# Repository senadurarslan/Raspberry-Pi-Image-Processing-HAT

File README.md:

# Raspberry Pi Image Processing HAT

A custom **Raspberry Pi 4 Model B HAT** designed for image capture, processing, and display using an **ArduCAM OV2640 camera**, **ST7735 TFT display**, and an **LM2596S-3.3 based switching power supply**.

## Project Overview

This project focuses on the design and implementation of a custom Hardware Attached on Top (**HAT**) board for the Raspberry Pi 4 Model B.

The system captures images using an **ArduCAM OV2640 camera**, processes the image data on the Raspberry Pi, and displays the resulting output on an **ST7735 TFT display**.

A custom PCB was designed to integrate the camera, display, Raspberry Pi GPIO interface, and power management circuitry into a compact embedded vision platform.

The main hardware blocks are:

- **Processing Unit:** Raspberry Pi 4 Model B
- **Image Capture:** ArduCAM Mini OV2640
- **Display:** ST7735 TFT
- **Power Management:** LM2596S-3.3 based SMPS
- **Custom Hardware:** Raspberry Pi HAT PCB

---

## System Architecture

The Raspberry Pi acts as the main processing and control unit.

The **ArduCAM OV2640** communicates with the Raspberry Pi using:

- **I²C** for camera sensor configuration
- **SPI** for image data transfer

The **ST7735 TFT display** uses:

- **SPI** for command and pixel data transfer
- GPIO signals for display control and reset

The overall image processing flow is:

```text
        ArduCAM OV2640
              │
       ┌──────┴──────┐
       │             │
      I²C           SPI
Configuration    Image Data
       │             │
       └──────┬──────┘
              ▼
       Raspberry Pi 4
              │
       JPEG Acquisition
              │
       Buffer Processing
              │
        JPEG Decoding
              │
       RGB565 Conversion
              │
              ▼
       ST7735 TFT Display
```

---

## Hardware Design

The custom HAT PCB was designed using **KiCad EDA**.

The hardware design includes:

- Raspberry Pi 40-pin GPIO interface
- ArduCAM OV2640 camera connector
- ST7735 TFT display connector
- LM2596S-3.3 switching regulator
- SPI communication lines
- I²C communication lines
- Dedicated chip-select signals
- Power distribution circuitry
- Ground plane for improved signal integrity
- SMD and THT components

The PCB was designed as a **two-layer board** and manufactured using the generated Gerber files.

After production, the components were assembled and the board was mounted directly onto the Raspberry Pi for functional testing.

---

## Power Management

An **LM2596S-3.3 based switching power supply (SMPS)** was integrated into the HAT design.

The power stage converts the available supply voltage to the required **3.3 V rail** for the peripheral hardware.

A switching regulator was preferred to provide:

- Higher energy efficiency
- Reduced thermal losses
- Stable output voltage
- Better performance under varying current loads
- Improved suitability for embedded applications

---

## Software Architecture

The software was developed using **C and C++** on Raspberry Pi OS.

The implementation includes:

- ArduChip communication
- OV2640 sensor initialization
- I²C communication
- SPI communication
- JPEG image acquisition
- JPEG file storage
- JPEG decoding
- RGB565 image conversion
- ST7735 TFT display control
- Camera and display integration
- Hardware test programs

### Main Source Files

```text
arduchip.c
arduchip.h

ov2640.c
ov2640.h
ov2640_regs.c
ov2640_regs.h

spi_linux.c
spi_linux.h

i2c_linux.c
i2c_linux.h

jpeg_to_rgb565.c
jpeg_to_rgb565.h

capture_to_file.c
capture_to_screen.cpp
decode_test.c

test_arduchip.c
test_hal.c
```

---

## Build System

The project includes a **Makefile** for compiling and running the camera, image processing, and TFT applications.

### Compilers

The project uses:

```text
gcc
g++
```

The full camera-to-display application is compiled using:

```text
-std=gnu++20
```

### Libraries

The TFT application uses:

```text
rpidisplaygl
lgpio
librt
```

with:

```text
/usr/local/include
/usr/local/lib
```

---

## Build & Run

### Show Available Commands

```bash
make
```

The default target displays the available build and run commands.

### Clean Build Files

```bash
make clean
```

This removes generated object files, executables, and temporary image files such as:

```text
frame.jpg
frame.rgb565
```

---

### ArduChip SPI Test

Compile:

```bash
make test_arduchip
```

Run:

```bash
make run_test_arduchip
```

This test verifies communication with the ArduChip interface.

---

### OV2640 Initialization Test

Compile:

```bash
make test_hal
```

Run:

```bash
make run_test_hal
```

This test verifies OV2640 initialization and communication through the hardware abstraction layer.

---

### Capture JPEG Image

Compile:

```bash
make capture_app
```

Run:

```bash
make run_capture_app
```

The application captures an image from the OV2640 camera and stores the acquired JPEG data.

---

### JPEG to RGB565 Conversion

Compile:

```bash
make decode_test
```

Run:

```bash
make run_decode_test
```

This application tests the conversion of captured JPEG image data into the **RGB565** pixel format used by the TFT display.

---

### Full Camera-to-TFT Pipeline

Compile:

```bash
make capture_screen
```

Run:

```bash
make run_capture_screen
```

This application combines the complete image pipeline:

```text
Camera
  ↓
JPEG Capture
  ↓
Image Processing
  ↓
RGB565 Conversion
  ↓
ST7735 TFT
```

---

# Project Gallery

## Final Integrated HAT System

The final implementation combines the custom HAT PCB, **ArduCAM OV2640 camera**, **ST7735 TFT display**, onboard power stage, and Raspberry Pi into a single integrated system.

---

## Camera Capture Test

The OV2640 camera was configured and tested on the Raspberry Pi.

Image data captured from the camera was transferred to the Raspberry Pi and successfully stored as a JPEG image.

The terminal output verifies the camera communication and image acquisition process, including:

```text
ArduChip SPI test OK
OV2640 init OK
Starting capture...
Capture done
Saved JPEG to frame.jpg
```

---

## Camera-to-TFT Integration Test

The image captured by the OV2640 camera was processed by the Raspberry Pi and displayed on the ST7735 TFT.

This test demonstrates the complete image pipeline from **camera acquisition to TFT visualization**.

---

## Testing

The system was tested incrementally before full integration.

The main test stages included:

- ArduChip SPI communication test
- OV2640 initialization test
- I²C sensor configuration
- SPI image data transfer
- JPEG image capture
- JPEG file storage
- JPEG decoding
- RGB565 conversion
- ST7735 graphical tests
- PCB electrical tests
- Camera and display integration
- Full system functional test

The final system successfully captured image data from the OV2640 camera, processed the image on the Raspberry Pi, and displayed the resulting image on the ST7735 TFT.

---

## PCB Development

The PCB development process consisted of:

```text
System Requirements
        ↓
Component Selection
        ↓
Schematic Design
        ↓
PCB Layout
        ↓
Gerber Generation
        ↓
PCB Manufacturing
        ↓
Component Assembly
        ↓
Electrical Testing
        ↓
Raspberry Pi Integration
        ↓
Functional Testing
```

The PCB design files and manufacturing outputs are included in the repository.

---

## Technologies & Tools

### Hardware

- Raspberry Pi 4 Model B
- ArduCAM OV2640
- ST7735 TFT
- LM2596S-3.3
- Custom Raspberry Pi HAT PCB

### Communication

- SPI
- I²C
- GPIO

### Software

- C
- C++
- GNU Make
- Raspberry Pi OS

### PCB Design

- KiCad EDA
- Gerber
- Two-layer PCB design

---

## Repository Contents

The repository contains:

```text
Raspberry-Pi-Image-Processing-HAT/
│
├── images/
│   ├── final_hat_system.jpg
│   ├── camera_capture_test.jpeg
│   └── camera_tft_test.jpeg
│
├── KiCad/
│   └── PCB and schematic design files
│
├── mühtas_1_project/
│   ├── Camera drivers
│   ├── SPI / I²C drivers
│   ├── Image processing files
│   ├── TFT application
│   └── Makefile
│
├── rapor/
│   └── Project documentation and reports
│
└── README.md
```

---

## Documentation

Detailed project documentation, design reports, system requirements, and test procedures are available in the repository.

The project documentation covers:

- System architecture
- Hardware design
- Power management
- Camera communication
- TFT communication
- PCB design
- Manufacturing
- Software development
- Integration
- Functional testing

---

## Project Context

This project was developed as part of the **MÜHTAS-1 Engineering Design Project** in the **Department of Electronics and Communication Engineering at Kocaeli University**.

The project combines embedded software development, digital communication interfaces, PCB design, power electronics, and image processing into a complete embedded vision system.

---

## Author

**Sena Sümeyye Durarslan**

Electronics and Communication Engineering  
Kocaeli University

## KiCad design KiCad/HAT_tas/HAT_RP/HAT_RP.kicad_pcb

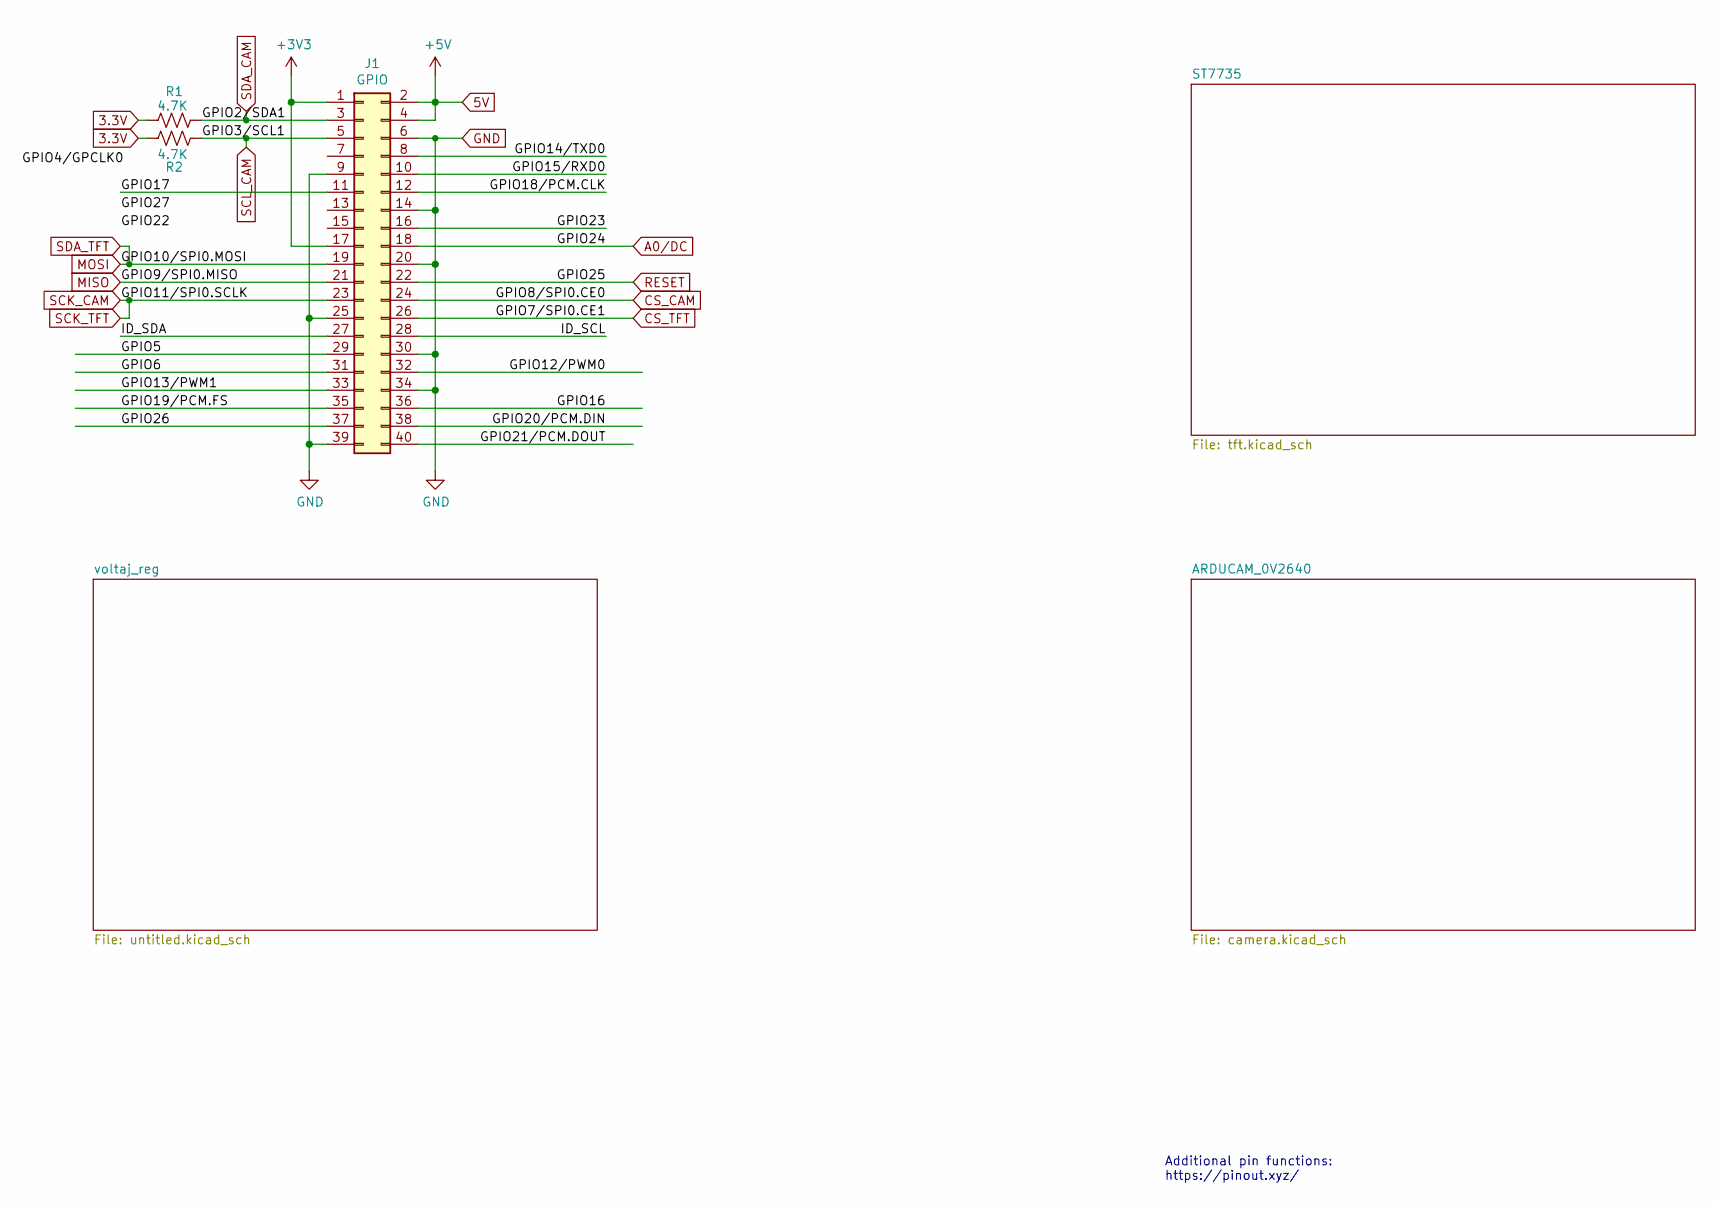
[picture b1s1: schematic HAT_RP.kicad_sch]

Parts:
J1: GPIO; PinSocket_2x20_P2.54mm_Vertical
R1, R2: 4.7K; R_0805_2012Metric

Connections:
3.3V: R1.1, R2.1; also elsewhere on the board
5V: J1.2, J1.4; also elsewhere on the board
+3V3: J1.1, J1.17
/GPIO5: J1.29
/GPIO6: J1.31
/GPIO12/PWM0: J1.32
/GPIO13/PWM1: J1.33
/GPIO14/TXD0: J1.8
/GPIO15/RXD0: J1.10
/GPIO16: J1.36
/GPIO17: J1.11
/GPIO18/PCM.CLK: J1.12
/GPIO19/PCM.FS: J1.35
/GPIO20/PCM.DIN: J1.38
/GPIO21/PCM.DOUT: J1.40
/GPIO23: J1.16
/GPIO26: J1.37
/ID_SCL: J1.28
/ID_SDA: J1.27
A0/DC: J1.18; also elsewhere on the board
CS_CAM: J1.24; also elsewhere on the board
CS_TFT: J1.26; also elsewhere on the board
GND: J1.6, J1.9, J1.14, J1.20, J1.25, J1.30, J1.34, J1.39; also elsewhere on the board
MISO: J1.21; also elsewhere on the board
MOSI: J1.19; also elsewhere on the board
RESET: J1.22; also elsewhere on the board
SCK_CAM: J1.23; also elsewhere on the board
SCL_CAM: J1.5, R2.2; also elsewhere on the board
SDA_CAM: J1.3, R1.2; also elsewhere on the board

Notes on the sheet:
Additional pin functions: https://pinout.xyz/

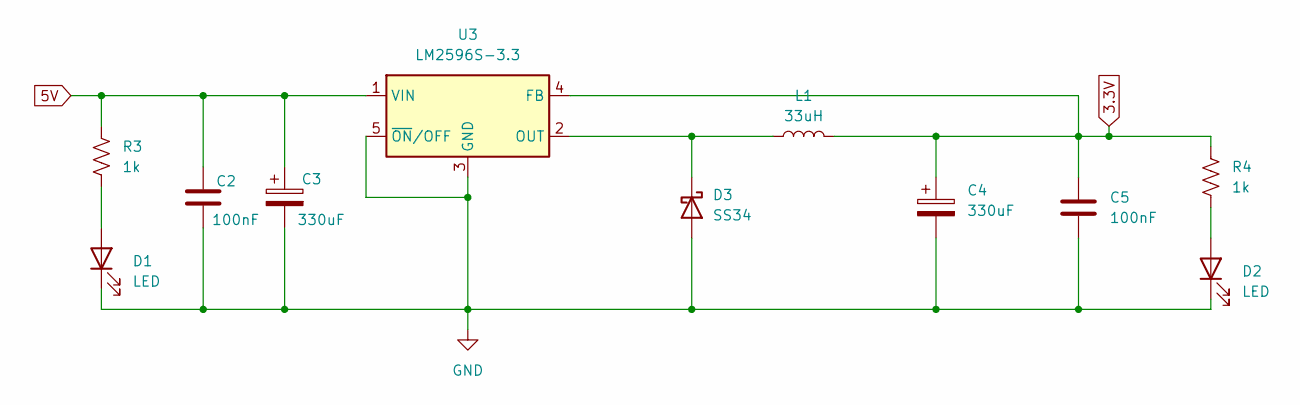
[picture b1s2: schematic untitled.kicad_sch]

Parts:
C2, C5: 100nF; C_0805_2012Metric
C3, C4: 330uF; CP_Elec_8x10
D1, D2: LED; LED_0805_2012Metric
D3: SS34; D_SMA
L1: 33uH; L_12x12mm_H8mm
R3, R4: 1k; R_0805_2012Metric
U3: LM2596S-3.3; TO-263-4

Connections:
3.3V: C4.1, C5.1, L1.2, R4.1, U3.4 (FB); also elsewhere on the board
5V: C2.1, C3.1, R3.1, U3.1 (VIN); also elsewhere on the board
GND: C2.2, C3.2, C4.2, C5.2, D1.1 (K), D2.1 (K), D3.2 (A), U3.3 (GND), U3.5 (~ON/OFF); also elsewhere on the board
unnamed: D1.2 (A), R3.2
unnamed: D2.2 (A), R4.2
unnamed: D3.1 (K), L1.1, U3.2 (OUT)

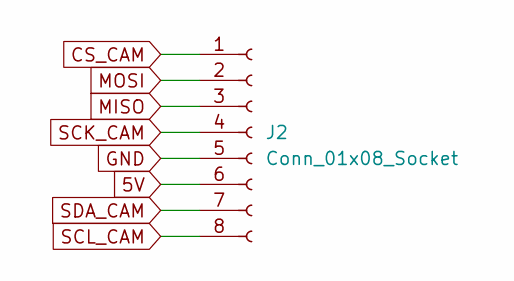
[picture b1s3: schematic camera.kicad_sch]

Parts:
J2: Conn_01x08_Socket; PinSocket_1x08_P2.54mm_Vertical

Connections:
5V: J2.6; also elsewhere on the board
CS_CAM: J2.1; also elsewhere on the board
GND: J2.5; also elsewhere on the board
MISO: J2.3; also elsewhere on the board
MOSI: J2.2; also elsewhere on the board
SCK_CAM: J2.4; also elsewhere on the board
SCL_CAM: J2.8; also elsewhere on the board
SDA_CAM: J2.7; also elsewhere on the board

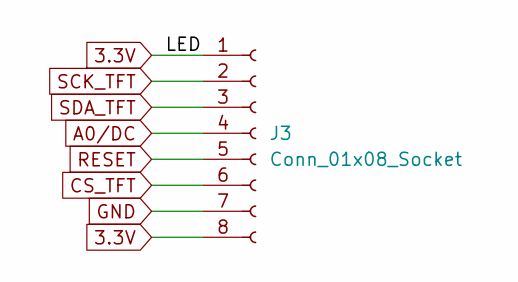
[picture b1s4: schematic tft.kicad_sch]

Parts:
J3: Conn_01x08_Socket; PinSocket_1x08_P2.54mm_Vertical

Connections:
3.3V: J3.1, J3.8; also elsewhere on the board
A0/DC: J3.4; also elsewhere on the board
CS_TFT: J3.6; also elsewhere on the board
GND: J3.7; also elsewhere on the board
MOSI: J3.3; also elsewhere on the board
RESET: J3.5; also elsewhere on the board
SCK_CAM: J3.2; also elsewhere on the board

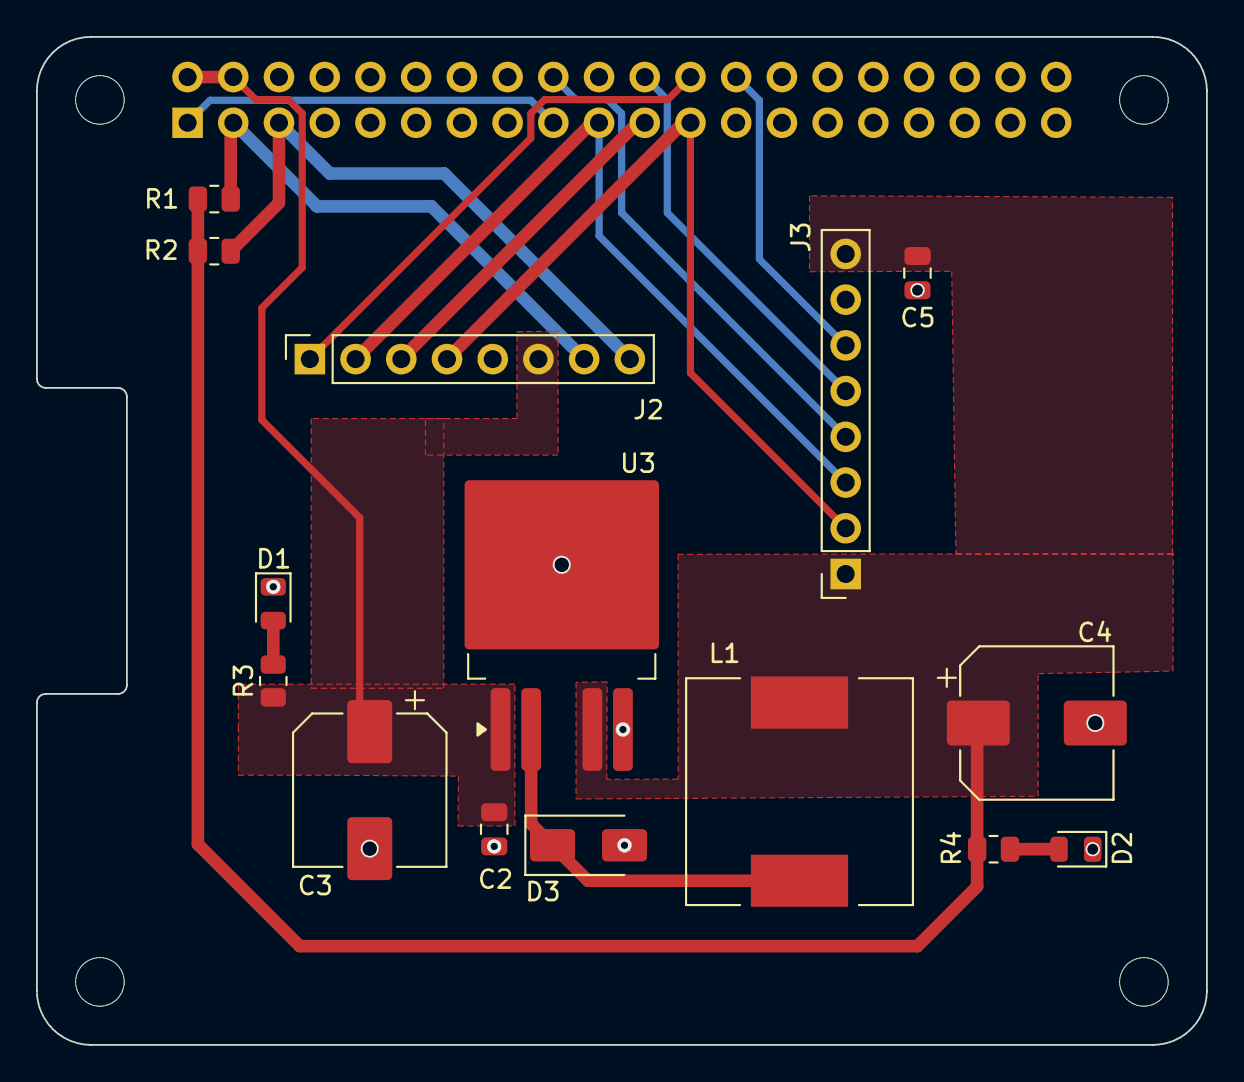
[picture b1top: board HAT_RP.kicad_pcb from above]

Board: 2 copper layers, 65.0 x 56.0 mm, 20 parts (1 on the bottom side), 16 nets.

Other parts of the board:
MH1, MH2, MH3, MH4: MountingHole_2.7mm_M2.5
